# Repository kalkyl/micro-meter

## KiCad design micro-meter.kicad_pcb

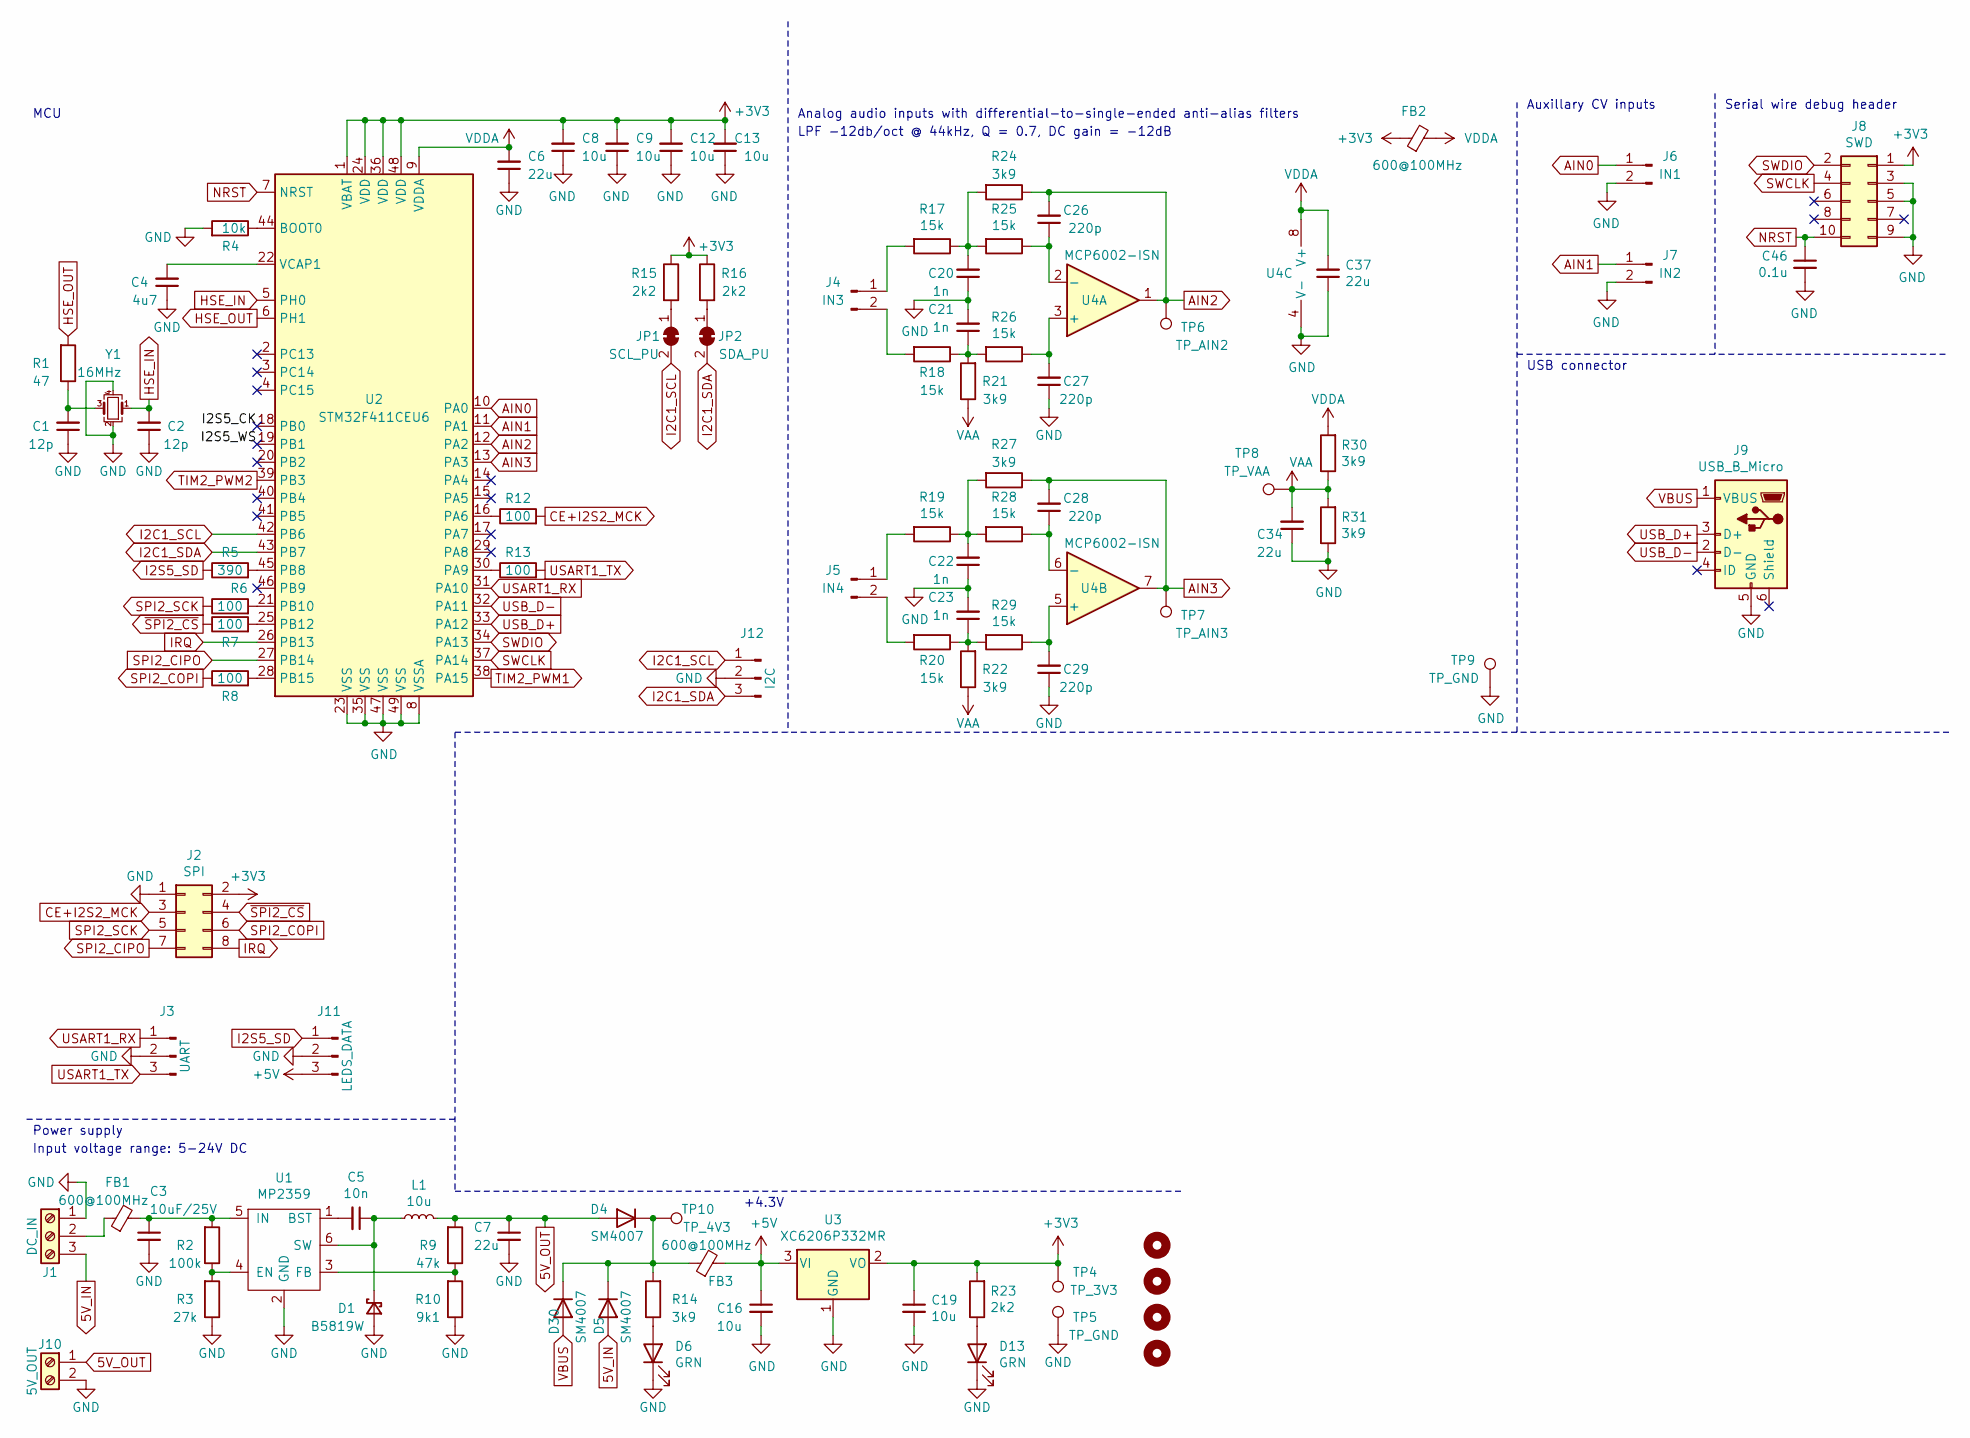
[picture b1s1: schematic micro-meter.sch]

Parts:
C1, C2: 12p; C_0402_1005Metric
C3: 10uF/25V; C_0805_2012Metric
C4: 4u7; C_0603_1608Metric
C5: 10n; C_0402_1005Metric
C6, C7, C34, C37: 22u; C_0603_1608Metric
C8, C9, C12, C13, C16, C19: 10u; C_0603_1608Metric
C20, C21, C22, C23: 1n; C_0603_1608Metric
C26, C27, C28, C29: 220p; C_0603_1608Metric
C46: 0.1u; C_0402_1005Metric
D1: B5819W; D_SOD-123
D4, D5, D30: SM4007; D_SOD-123F
D6, D13: GRN; LED_0805_2012Metric
FB1, FB2, FB3: 600@100MHz; L_0805_2012Metric
H1, H2, H3, H4: MountingHole; MountingHole_3.2mm_M3
J1: DC_IN; PinSocket_1x03_P2.54mm_Vertical
J2: SPI; PinSocket_2x04_P2.54mm_Vertical
J3: UART; PinSocket_1x03_P2.54mm_Vertical
J4: IN3; PinSocket_1x02_P2.54mm_Vertical
J5: IN4; PinSocket_1x02_P2.54mm_Vertical
J6: IN1; PinSocket_1x02_P2.54mm_Vertical
J7: IN2; PinSocket_1x02_P2.54mm_Vertical
J8: SWD; PinHeader_2x05_P1.27mm_Vertical
J9: USB_B_Micro; USB_Micro-B_Wuerth_629105150521
J10: 5V_OUT; PinHeader_1x02_P2.54mm_Vertical
J11: LEDS_DATA; PinHeader_1x03_P2.54mm_Vertical
J12: I2C; PinSocket_1x03_P2.54mm_Vertical
JP1: SCL_PU; SolderJumper-2_P1.3mm_Open_RoundedPad1.0x1.5mm
JP2: SDA_PU; SolderJumper-2_P1.3mm_Open_RoundedPad1.0x1.5mm
L1: 10u; L_Sunlord_MWSA0518_5.4x5.2mm
R1: 47; R_0402_1005Metric
R2: 100k; R_0402_1005Metric
R3: 27k; R_0402_1005Metric
R4: 10k; R_0402_1005Metric
R5: 390; R_0402_1005Metric
R6, R7, R8, R12, R13: 100; R_0402_1005Metric
R9: 47k; R_0402_1005Metric
R10: 9k1; R_0603_1608Metric
R14, R21, R22, R24, R27, R30, R31: 3k9; R_0603_1608Metric
R15, R16, R23: 2k2; R_0603_1608Metric
R17, R18, R19, R20, R25, R26, R28, R29: 15k; R_0603_1608Metric
TP4: TP_3V3; TestPoint_Pad_2.0x2.0mm
TP5, TP9: TP_GND; TestPoint_Loop_D2.50mm_Drill1.0mm
TP6: TP_AIN2; TestPoint_Pad_2.0x2.0mm
TP7: TP_AIN3; TestPoint_Pad_2.0x2.0mm
TP8: TP_VAA; TestPoint_Pad_2.0x2.0mm
TP10: TP_4V3; TestPoint_Pad_2.0x2.0mm
U1: MP2359; TSOT-23-6
U2: STM32F411CEU6; QFN-48-1EP_7x7mm_P0.5mm_EP5.6x5.6mm
U3: XC6206P332MR; SOT-23
U4: MCP6002-ISN; SOIC-8_3.9x4.9mm_P1.27mm
Y1: 16MHz; Crystal_SMD_3225-4Pin_3.2x2.5mm

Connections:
5V_IN: D5.2 (A), J1.3
5V_OUT: C7.1, D4.2 (A), J10.1, L1.2, R9.2
+3V3: C8.2, C9.2, C12.2, C13.2, C19.1, FB2.1, J2.2, J8.1, R15.1, R16.1, R23.2, TP4.1, U2.1 (VBAT), U2.24 (VDD), U2.36 (VDD), U2.48 (VDD), U3.2 (VO)
+5V: C16.1, FB3.2, J11.3, U3.3 (VI)
/I2S5_CK: U2.18 (PB0)
/I2S5_WS: U2.19 (PB1)
AIN0: J6.1, U2.10 (PA0)
AIN1: J7.1, U2.11 (PA1)
AIN2: C26.2, R24.1, TP6.1, U2.12 (PA2), U4.1
AIN3: C28.2, R27.1, TP7.1, U2.13 (PA3), U4.7
CE+I2S2_MCK: J2.3, R12.2
GND: C1.1, C2.1, C3.2, C4.1, C6.1, C7.2, C8.1, C9.1, C12.1, C13.1, C16.2, C19.2, C20.1, C21.2, C22.1, C23.2, C27.1, C29.1, C34.1, C37.1, C46.2, D1.2 (A), D6.1 (K), D13.1 (K), J1.1, J2.1, J3.2, J6.2, J7.2, J8.3, J8.5, J8.9, J9.5 (GND), J10.2, J11.2, J12.2, R3.1, R4.2, R10.1, R31.1, TP5.1, TP9.1, U1.2 (GND), U2.8 (VSSA), U2.23 (VSS), U2.35 (VSS), U2.47 (VSS), U2.49 (VSS), U3.1 (GND), U4.4 (V-), Y1.2, Y1.4
HSE_IN: C2.2, U2.5 (PH0), Y1.1
HSE_OUT: R1.2, U2.6 (PH1)
I2C1_SCL: J12.1, JP1.2 (B), U2.42 (PB6)
I2C1_SDA: J12.3, JP2.2 (B), U2.43 (PB7)
I2S5_SD: J11.1, R5.1
IRQ: J2.8, U2.26 (PB13)
NRST: C46.1, J8.10, U2.7 (NRST)
unnamed: C1.2, R1.1, Y1.3
unnamed: C3.1, FB1.2, R2.2, U1.5 (IN)
unnamed: C4.2, U2.22 (VCAP1)
unnamed: C5.1, D1.1 (K), L1.1, U1.6 (SW)
unnamed: C5.2, U1.1 (BST)
unnamed: C20.2, R17.1, R24.2, R25.2
unnamed: C21.1, R18.1, R21.2, R26.2
unnamed: C22.2, R19.1, R27.2, R28.2
unnamed: C23.1, R20.1, R22.2, R29.2
unnamed: C26.1, R25.1, U4.2 (-)
unnamed: C27.2, R26.1, U4.3 (+)
unnamed: C28.1, R28.1, U4.6 (-)
unnamed: C29.2, R29.1, U4.5 (+)
unnamed: D6.2 (A), R14.1
unnamed: D13.2 (A), R23.1
unnamed: D4.1 (K), D5.1 (K), D30.1 (K), FB3.1, R14.2, TP10.1
unnamed: FB1.1, J1.2
unnamed: J4.1, R17.2
unnamed: J4.2, R18.2
unnamed: J5.1, R19.2
unnamed: J5.2, R20.2
unnamed: JP1.1 (A), R15.2
unnamed: JP2.1 (A), R16.2
unnamed: R2.1, R3.2, U1.4 (EN)
unnamed: R4.1, U2.44 (BOOT0)
unnamed: R5.2, U2.45 (PB8)
unnamed: R6.2, U2.21 (PB10)
unnamed: R7.2, U2.25 (PB12)
unnamed: R8.2, U2.28 (PB15)
unnamed: R9.1, R10.2, U1.3 (FB)
unnamed: R12.1, U2.16 (PA6)
unnamed: R13.1, U2.30 (PA9)
SPI2_CIPO: J2.7, U2.27 (PB14)
SPI2_COPI: J2.6, R8.1
SPI2_SCK: J2.5, R6.1
SWCLK: J8.4, U2.37 (PA14)
SWDIO: J8.2, U2.34 (PA13)
TIM2_PWM1: U2.38 (PA15)
TIM2_PWM2: U2.39 (PB3)
USART1_RX: J3.1, U2.31 (PA10)
USART1_TX: J3.3, R13.2
USB_D+: J9.3 (D+), U2.33 (PA12)
USB_D-: J9.2 (D-), U2.32 (PA11)
VAA: C34.2, R21.1, R22.1, R30.1, R31.2, TP8.1
VBUS: D30.2 (A), J9.1 (VBUS)
VDDA: C6.2, C37.2, FB2.2, R30.2, U2.9 (VDDA), U4.8 (V+)
~SPI2_CS: J2.4, R7.1

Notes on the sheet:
Serial wire debug header
USB connector
MCU
Power supply
Analog audio inputs with differential-to-single-ended anti-alias filters
Auxillary CV inputs
LPF -12db/oct @ 44kHz, Q = 0.7, DC gain = -12dB
+4.3V
Input voltage range: 5-24V DC

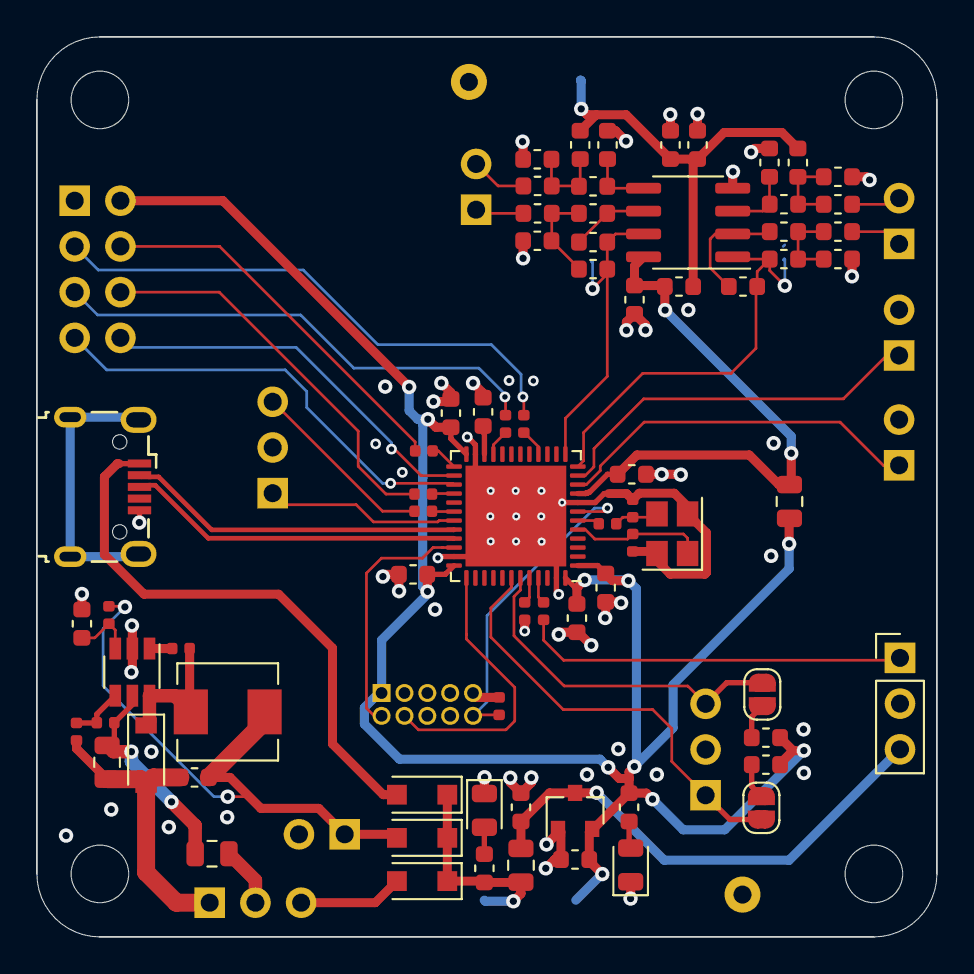
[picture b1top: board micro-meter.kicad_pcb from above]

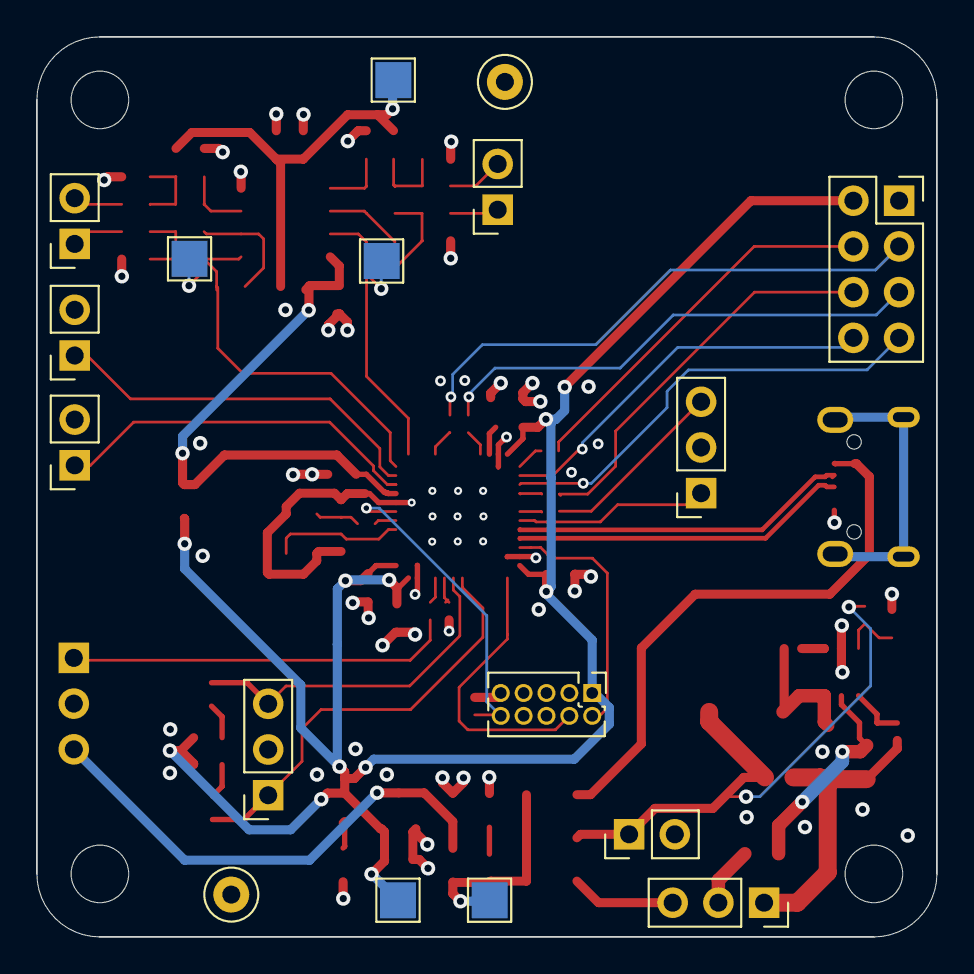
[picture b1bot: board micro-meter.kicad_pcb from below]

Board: 4 copper layers, 50.0 x 50.0 mm, 94 parts (17 on the bottom side), 62 nets.

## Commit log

2020-11-04 Add schematics
2020-11-04 Add MFB anti-alias filters
2020-11-04 Cleanup schematics, add text
2020-11-04 Cleanup schematics
2020-11-06 Assign MCU pins
2020-11-06 Fix net labels
2020-11-06 Fix testpoints
2020-11-06 Add series terminations
2020-11-06 Add testpoints
2020-11-07 Annotate and assign footprints
2020-11-07 Add crystal and i2c pullups
2020-11-07 Change to 0402 footprints
2020-11-07 Add buck regulator
2020-11-07 Cleanup schematic
2020-11-07 Fix buck reg FB values
2020-11-07 Change buck inductor value
2020-11-08 Layout blocks
2020-11-10 Rough layout
2020-11-11 Cleanup layout
2020-11-11 Move references to fab layers
2020-11-11 Add inner layers and planes
2020-11-11 Add rounded corners
2020-11-11 Add design rules and default track/via sizes
2020-11-17 Add routing
2020-11-17 Cleanup routing
